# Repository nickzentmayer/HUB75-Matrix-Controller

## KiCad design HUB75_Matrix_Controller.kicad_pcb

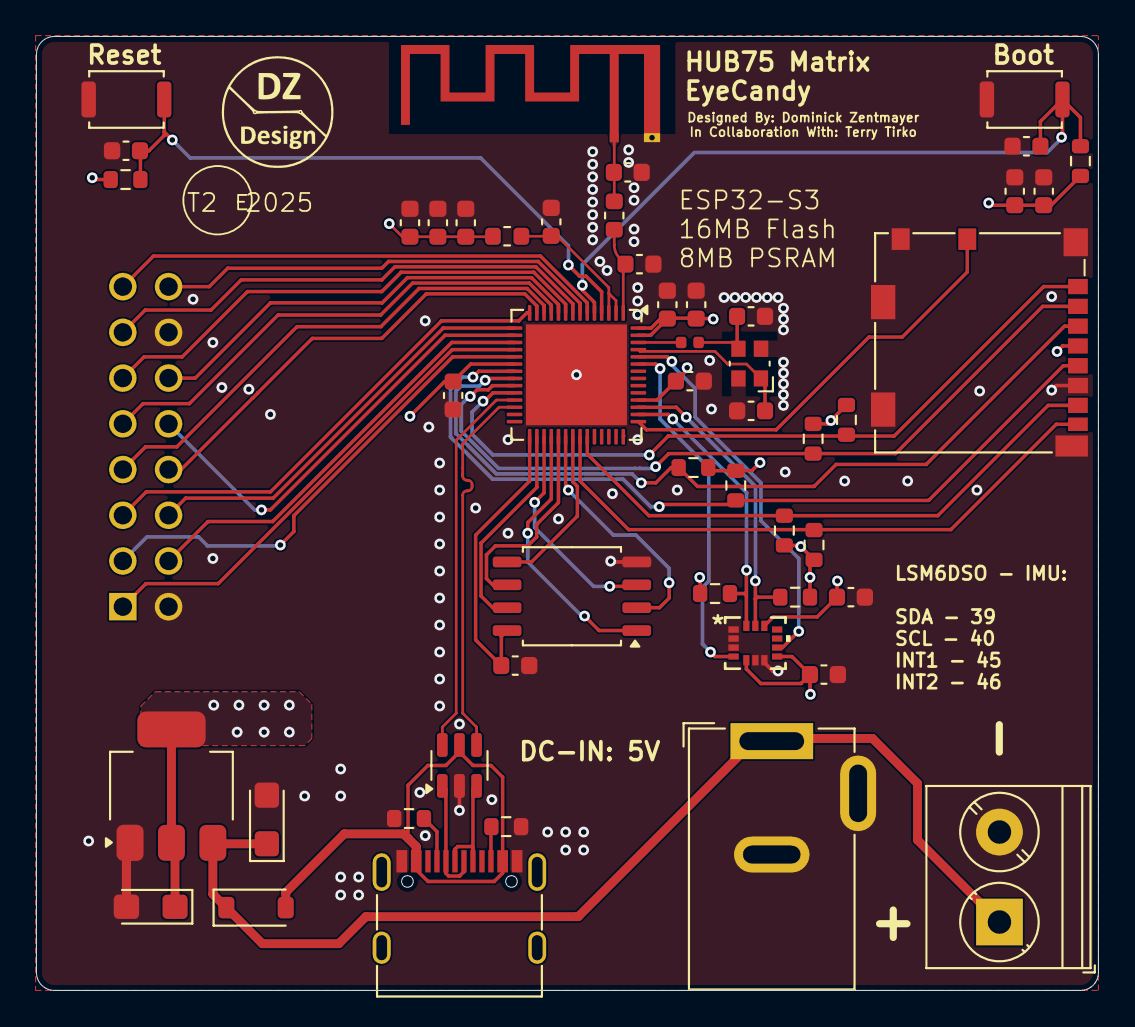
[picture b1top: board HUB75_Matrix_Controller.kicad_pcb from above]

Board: 4 copper layers, 59.0 x 53.0 mm, 51 parts (1 on the bottom side), 50 nets.

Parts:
C1, C4, C5, C7, C12, C13, C14, C15, C21: 100nF; C_0603_1608Metric
C2, C3: 22uF; CP_EIA-3216-10_Kemet-I
C6, C11, C17, C20: 1uF; C_0603_1608Metric
C8, C9: 1.8pF; C_0603_1608Metric
C10: 10uF; C_0603_1608Metric
C16: 10nF; C_0603_1608Metric
C18, C19: 12pF; C_0603_1608Metric
D1: MBR0540; D_SOD-123
J1: USB_C_Receptacle_USB2.0_16P; USB_C_Receptacle_G-Switch_GT-USB-7010ASV
J2: Barrel_Jack_MountingPin; BarrelJack_GCT_DCJ200-10-A_Horizontal
J3: Screw_Terminal_01x02; TerminalBlock_Phoenix_PT-1,5-2-5.0-H_1x02_P5.00mm_Horizontal
J4: Micro_SD_Card_Det2; microSD_HC_Molex_104031-0811
J5: SFH11-PBPC-D08-ST-BK; SULLINS_SFH11-PBPC-D08-ST-BK
L1: 2.4nH; L_0603_1608Metric
L2: 22nH; L_0402_1005Metric
L3: 2.0nH; L_0603_1608Metric
R1, R2: 5.1k; R_0603_1608Metric
R3, R4, R5, R6, R7, R8, R9, R10, R13, R14: 10k; R_0603_1608Metric
SW1: EN; SW_Push_SPST_NO_Alps_SKRK
SW2: BOOT; SW_Push_SPST_NO_Alps_SKRK
U1: LSM6DSOTR; LGA-14L_2P5X3X0P86_STM
U2: AMS1117-3.3; SOT-223-3_TabPin2
U3: USBLC6-2SC6; SOT-23-6
U4: W25Q128JVS; SOIC-8_5.23x5.23mm_P1.27mm
U5: Texas_SWRA117D_2.4GHz_Left
U6: ESP32-S3; QFN-56-1EP_7x7mm_P0.4mm_EP5.6x5.6mm
X1: 40MHz; Crystal_SMD_Abracon_ABM10-4Pin_2.5x2.0mm

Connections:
+3V3: C1.1, C3.1, C4.1, C6.1, C7.1, C10.1, C11.1, C12.1, C13.1, C15.1, C16.1, C17.1, J4.4 (VDD), L3.1, R3.1, R4.1, R5.1, R6.1, R7.1, R8.1, R9.1, R10.1, R13.1, R14.1, U1.5 (VDDIO), U1.8 (VDD), U1.12 (CS), U2.2 (VO), U6.20 (VDD3P3_RTC), U6.46 (VDD3P3_CPU), U6.55 (VDDA), U6.56 (VDDA)
+5V: C2.1, D1.1 (K), J2.1, J3.1, U2.3 (VI)
A: J5.7, U6.12 (GPIO7/ADC1_CH6)
B: J5.8, U6.13 (GPIO8/ADC1_CH7)
B1: J5.13, U6.8 (GPIO3/ADC1_CH2)
B2: J5.9, U6.11 (GPIO6/ADC1_CH5)
BOOT: C21.1, R14.2, SW2.2, U6.5 (GPIO0/BOOT)
C: J5.5, U6.14 (GPIO9/ADC1_CH8)
CLK: J5.3, U6.19 (GPIO14/ADC2_CH3)
CMD: J4.3 (CMD), R8.2, U6.22 (GPIO16/ADC2_CH5/XTAL_32K_N)
D: J5.6, U6.15 (GPIO10/ADC1_CH9)
D0: J4.7 (DAT0), R7.2, U6.37 (SPICLK_P/GPIO47)
D1: J4.8 (DAT1), R6.2, U6.36 (SPICLK_N/GPIO48)
D2: J4.1 (DAT2), R10.2, U6.24 (GPIO18/ADC2_CH7)
D3: J4.2 (DAT3/CD), R9.2, U6.23 (GPIO17/ADC2_CH6)
D+: U3.4 (I/O2), U6.26 (GPIO20/USB_D+/ADC2_CH9)
D-: U3.6 (I/O1), U6.25 (GPIO19/USB_D-/ADC2_CH8)
DET: J4.9 (DET_B), U6.43 (GPIO38)
E: J5.10, U6.16 (GPIO11/ADC2_CH0)
EN: C20.1, R13.2, SW1.2, U6.4 (CHIP_PU/RESET)
G1: J5.16, U6.7 (GPIO2/ADC1_CH1)
G2: J5.12, U6.10 (GPIO5/ADC1_CH4)
GND: C1.2, C2.2, C3.2, C4.2, C5.2, C6.2, C7.2, C8.2, C9.2, C10.2, C11.2, C12.2, C13.2, C14.2, C15.2, C16.2, C17.2, C18.2, C19.2, C20.2, C21.2, J1.A1 (GND), J1.A12 (GND), J1.B1 (GND), J1.B12 (GND), J2.2, J2.3 (MountPin), J3.2, J4.6 (VSS), J4.10 (DET_A), J4.11 (SHIELD), J5.2, J5.14, R1.1, R2.1, SW1.1, SW2.1, U1.1 (SDO/SA0), U1.2 (SDx), U1.3 (SCx), U1.6 (GND), U1.7 (GND), U2.1 (GND), U3.2 (GND), U4.4 (GND), U5.1, U6.57 (GND), X1.2, X1.4
INT1: U1.4 (INT1), U6.51 (GPIO45)
INT2: U1.9 (INT2), U6.52 (GPIO46)
LAT: J5.4, U6.17 (GPIO12/ADC2_CH1)
LNA: C9.1, L1.1, U6.1 (LNA_IN/RF)
unnamed: J1.A5 (CC1), R1.2
unnamed: J1.B5 (CC2), R2.2
unnamed: J1.A6 (D+), J1.B6 (D+), U3.3 (I/O2)
unnamed: J1.A7 (D-), J1.B7 (D-), U3.1 (I/O1)
unnamed: U4.6 (CLK), U6.33 (SPICLK/GPIO30)
unnamed: U4.5 (DI(IO0)), U6.35 (SPID/GPIO32)
unnamed: U4.2 (DO(IO1)), U6.34 (SPIQ/GPIO31)
unnamed: U4.3 (IO2), U6.31 (SPIWP/GPIO28)
unnamed: U4.7 (IO3), U6.30 (SPIHD/GPIO27)
unnamed: U4.1 (~CS), U6.32 (SPICS0/GPIO29)
unnamed: C8.1, L1.2, U5.2 (FP)
unnamed: L2.2, U6.54 (XTAL_P)
OE: J5.1, U6.18 (GPIO13/ADC2_CH2)
R1: J5.15, U6.6 (GPIO1/ADC1_CH0)
R2: J5.11, U6.9 (GPIO4/ADC1_CH3)
SCL: R4.2, U1.13 (SCL), U6.45 (MTDO/JTAG/GPIO40)
SDA: R3.2, U1.14 (SDA), U6.44 (MTCK/JTAG/GPIO39)
SD_CLK: J4.5 (CLK), R5.2, U6.21 (GPIO15/ADC2_CH4/XTAL_32K_P)
VBUS: D1.2 (A), J1.A4 (VBUS), J1.A9 (VBUS), J1.B4 (VBUS), J1.B9 (VBUS), U3.5 (VBUS)
VDD3P3: C14.1, L3.2, U6.2 (VDD3P3), U6.3 (VDD3P3)
VDD_SDIO: C5.1, U4.8 (VCC), U6.29 (VDD_SPI)
XTAL_N: C18.1, U6.53 (XTAL_N), X1.1
XTAL_P: C19.1, L2.1, X1.3

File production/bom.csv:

Designator,Footprint,Quantity,Value,LCSC Part #
"C1, C12, C13, C14, C15, C21, C24, C25, C4, C5, C7",0603,11,100nF,
C10,0603,1,10uF,
"C11, C17, C20, C22, C23, C6",0603,6,1uF,
C16,0603,1,10nF,
"C18, C19",0603,2,12pF,
"C2, C3",CP_EIA-3216-10_Kemet-I,2,22uF,
"C8, C9",0603,2,1.8pF,
D1,D_SOD-123,1,MBR0540,
J1,USB_C_Receptacle_G-Switch_GT-USB-7010ASV,1,USB_C_Receptacle_USB2.0_16P,
J2,BarrelJack_GCT_DCJ200-10-A_Horizontal,1,Barrel_Jack_MountingPin,
J3,"TerminalBlock_Phoenix_PT-1,5-2-5.0-H_1x02_P5.00mm_Horizontal",1,Screw_Terminal_01x02,
J4,microSD_HC_Molex_104031-0811,1,Micro_SD_Card_Det2,
J5,SULLINS_SFH11-PBPC-D08-ST-BK,1,SFH11-PBPC-D08-ST-BK,
L1,0603,1,2.4nH,
L2,0402,1,22nH,
L3,0603,1,2.0nH,
"R1, R2",0603,2,5.1k,
"R10, R11, R12, R13, R14, R15, R16, R3, R4, R5, R6, R7, R8, R9",0603,14,10k,
SW1,SW_Push_SPST_NO_Alps_SKRK,1,EN,
SW2,SW_Push_SPST_NO_Alps_SKRK,1,BOOT,
U1,LGA-14L_2P5X3X0P86_STM,1,LSM6DSOTR,
U2,SOT-223-3_TabPin2,1,AMS1117-3.3,
U3,SOT-23-6,1,USBLC6-2SC6,
U4,SOIC-8_5.23x5.23mm_P1.27mm,1,W25Q128JVS,
U5,Texas_SWRA117D_2.4GHz_Left,1,~,
U6,QFN-56-1EP_7x7mm_P0.4mm_EP5.6x5.6mm,1,ESP32-S3,
"U7, U8",PW20,2,SN74HCT245PWR,
X1,Crystal_SMD_Abracon_ABM10-4Pin_2.5x2.0mm,1,40MHz,

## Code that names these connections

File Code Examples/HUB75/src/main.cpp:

#include <Arduino.h>
#include "FS.h"
#include "SD_MMC.h"


void listDir(fs::FS &fs, const char *dirname, uint8_t levels) {
  Serial.printf("Listing directory: %s\n", dirname);

  File root = fs.open(dirname);
  if (!root) {
    Serial.println("Failed to open directory");
    return;
  }
  if (!root.isDirectory()) {
    Serial.println("Not a directory");
    return;
  }

  File file = root.openNextFile();
  while (file) {
    if (file.isDirectory()) {
      Serial.print("  DIR : ");
      Serial.println(file.name());
      if (levels) {
        listDir(fs, file.path(), levels - 1);
      }
    } else {
      Serial.print("  FILE: ");
      Serial.print(file.name());
      Serial.print("  SIZE: ");
      Serial.println(file.size());
    }
    file = root.openNextFile();
  }
}

void createDir(fs::FS &fs, const char *path) {
  Serial.printf("Creating Dir: %s\n", path);
  if (fs.mkdir(path)) {
    Serial.println("Dir created");
  } else {
    Serial.println("mkdir failed");
  }
}

void removeDir(fs::FS &fs, const char *path) {
  Serial.printf("Removing Dir: %s\n", path);
  if (fs.rmdir(path)) {
    Serial.println("Dir removed");
  } else {
    Serial.println("rmdir failed");
  }
}

void readFile(fs::FS &fs, const char *path) {
  Serial.printf("Reading file: %s\n", path);

  File file = fs.open(path);
  if (!file) {
    Serial.println("Failed to open file for reading");
    return;
  }

  Serial.print("Read from file: ");
  while (file.available()) {
    Serial.write(file.read());
  }
}

void writeFile(fs::FS &fs, const char *path, const char *message) {
  Serial.printf("Writing file: %s\n", path);

  File file = fs.open(path, FILE_WRITE);
  if (!file) {
    Serial.println("Failed to open file for writing");
    return;
  }
  if (file.print(message)) {
    Serial.println("File written");
  } else {
    Serial.println("Write failed");
  }
}

void appendFile(fs::FS &fs, const char *path, const char *message) {
  Serial.printf("Appending to file: %s\n", path);

  File file = fs.open(path, FILE_APPEND);
  if (!file) {
    Serial.println("Failed to open file for appending");
    return;
  }
  if (file.print(message)) {
    Serial.println("Message appended");
  } else {
    Serial.println("Append failed");
  }
}

void renameFile(fs::FS &fs, const char *path1, const char *path2) {
  Serial.printf("Renaming file %s to %s\n", path1, path2);
  if (fs.rename(path1, path2)) {
    Serial.println("File renamed");
  } else {
    Serial.println("Rename failed");
  }
}

void deleteFile(fs::FS &fs, const char *path) {
  Serial.printf("Deleting file: %s\n", path);
  if (fs.remove(path)) {
    Serial.println("File deleted");
  } else {
    Serial.println("Delete failed");
  }
}

void testFileIO(fs::FS &fs, const char *path) {
  File file = fs.open(path);
  static uint8_t buf[512];
  size_t len = 0;
  uint32_t start = millis();
  uint32_t end = start;
  if (file) {
    len = file.size();
    size_t flen = len;
    start = millis();
    while (len) {
      size_t toRead = len;
      if (toRead > 512) {
        toRead = 512;
      }
      file.read(buf, toRead);
      len -= toRead;
    }
    end = millis() - start;
    Serial.printf("%u bytes read for %lu ms\n", flen, end);
    file.close();
  } else {
    Serial.println("Failed to open file for reading");
  }

  file = fs.open(path, FILE_WRITE);
  if (!file) {
    Serial.println("Failed to open file for writing");
    return;
  }

  size_t i;
  start = millis();
  for (i = 0; i < 2048; i++) {
    file.write(buf, 512);
  }
  end = millis() - start;
  Serial.printf("%u bytes written for %lu ms\n", 2048 * 512, end);
  file.close();
}

void setup() {
  Serial.begin(115200);
  pinMode(r1, OUTPUT);
  pinMode(r2, OUTPUT);
  pinMode(g1, OUTPUT);
  pinMode(g2, OUTPUT);
  pinMode(b1, OUTPUT);
  pinMode(b2, OUTPUT);
    pinMode(A, OUTPUT);
    pinMode(B, OUTPUT);
    pinMode(C, OUTPUT);
    pinMode(D, OUTPUT);
    pinMode(E, OUTPUT);
    pinMode(LAT, OUTPUT);
    pinMode(OE, OUTPUT);
    pinMode(CLK, OUTPUT);
  pinMode(SD_DET, INPUT_PULLUP);
  while(digitalRead(SD_DET) == HIGH){
    Serial.println("Waiting for SD card to be inserted");
    delay(1000);
  }
  /*
    // If you want to change the pin assignment or you get an error that some pins
    // are not assigned on ESP32-S3/ESP32-P4 uncomment this block and the appropriate
    // line depending if you want to use 1-bit or 4-bit line.
    // Please note that ESP32 does not allow pin change and setPins() will always fail.
    //if(! SD_MMC.setPins(clk, cmd, d0)){
    //if(! SD_MMC.setPins(clk, cmd, d0, d1, d2, d3)){
    //    Serial.println("Pin change failed!");
    //    return;
    //}
  */
 //SD_MMC.setPins(34, 35, 33, 47, 37, 36);
 SD_MMC.setPins(SD_CLK, SD_CMD, SD_D0, SD_D1, SD_D2, SD_D3);
digitalWrite(r1, HIGH);
digitalWrite(r2, 1);
digitalWrite(g1, 1);
digitalWrite(g2, 1);
digitalWrite(b1, 1);
digitalWrite(b2, 1);
digitalWrite(A, 1);
digitalWrite(B, 1);
digitalWrite(C, 1);
digitalWrite(D, 1);
digitalWrite(E, 1);
digitalWrite(LAT, 1);
digitalWrite(OE, 1);
digitalWrite(CLK, 1);


  if (!SD_MMC.begin()) {
    Serial.println("Card Mount Failed");
    return;
  }
  uint8_t cardType = SD_MMC.cardType();

  if (cardType == CARD_NONE) {
    Serial.println("No SD_MMC card attached");
    return;
  }

  Serial.print("SD_MMC Card Type: ");
  if (cardType == CARD_MMC) {
    Serial.println("MMC");
  } else if (cardType == CARD_SD) {
    Serial.println("SDSC");
  } else if (cardType == CARD_SDHC) {
    Serial.println("SDHC");
  } else {
    Serial.println("UNKNOWN");
  }

  uint64_t cardSize = SD_MMC.cardSize() / (1024 * 1024);
  Serial.printf("SD_MMC Card Size: %lluMB\n", cardSize);

  listDir(SD_MMC, "/", 0);
  createDir(SD_MMC, "/mydir");
  listDir(SD_MMC, "/", 0);
  removeDir(SD_MMC, "/mydir");
  listDir(SD_MMC, "/", 2);
  writeFile(SD_MMC, "/hello.txt", "Hello ");
  appendFile(SD_MMC, "/hello.txt", "World!\n");
  readFile(SD_MMC, "/hello.txt");
  deleteFile(SD_MMC, "/foo.txt");
  renameFile(SD_MMC, "/hello.txt", "/foo.txt");
  readFile(SD_MMC, "/foo.txt");
  testFileIO(SD_MMC, "/test.txt");
  Serial.printf("Total space: %lluMB\n", SD_MMC.totalBytes() / (1024 * 1024));
  Serial.printf("Used space: %lluMB\n", SD_MMC.usedBytes() / (1024 * 1024));
}

void loop() {
  delay(10);
  Serial.println("Loop");
}

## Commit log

2025-02-07 Initial Commit
    Version 1
2025-02-11 ESP -> HUB75
    Option to ignore Level Shifter
2025-02-14 Silkscreen Updates
2025-03-07 v2, fixed SD and USB
2025-03-26 v1.0
2025-03-27 v1.1, final changes
2025-03-30 Added code examples
2025-05-05 Removed level shifters | Added code examples
